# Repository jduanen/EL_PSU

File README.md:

# EL_PSU
High Voltage Power Supply Unit for EL Displays

This is a modification of the most excellent work of Ben Krasnow at https://github.com/benkrasnow/EL_driver_multi

The primary motivation for these changes are to better support the needs of the EL displays found in https://github.com/jduanen/alienFontDisplay and https://github.com/jduanen/elClock.
In particular, to extend the life of these displays, I want to create a triangle (as opposed to, step) waveform so that the dv/dt of the signal exciting the display segments remains (close to) constant.

**WIP**

#### Parts Kitting

* Digikey Cart: https://www.digikey.com/short/m9prqmhq
  - look at datasheets and make sure substitutions work
    * B0540W Schottky diode not in stock at Digikey, substituting B0540W RHG
    * MMBD5004S-7DICT-ND is an obsolete item at Digikey

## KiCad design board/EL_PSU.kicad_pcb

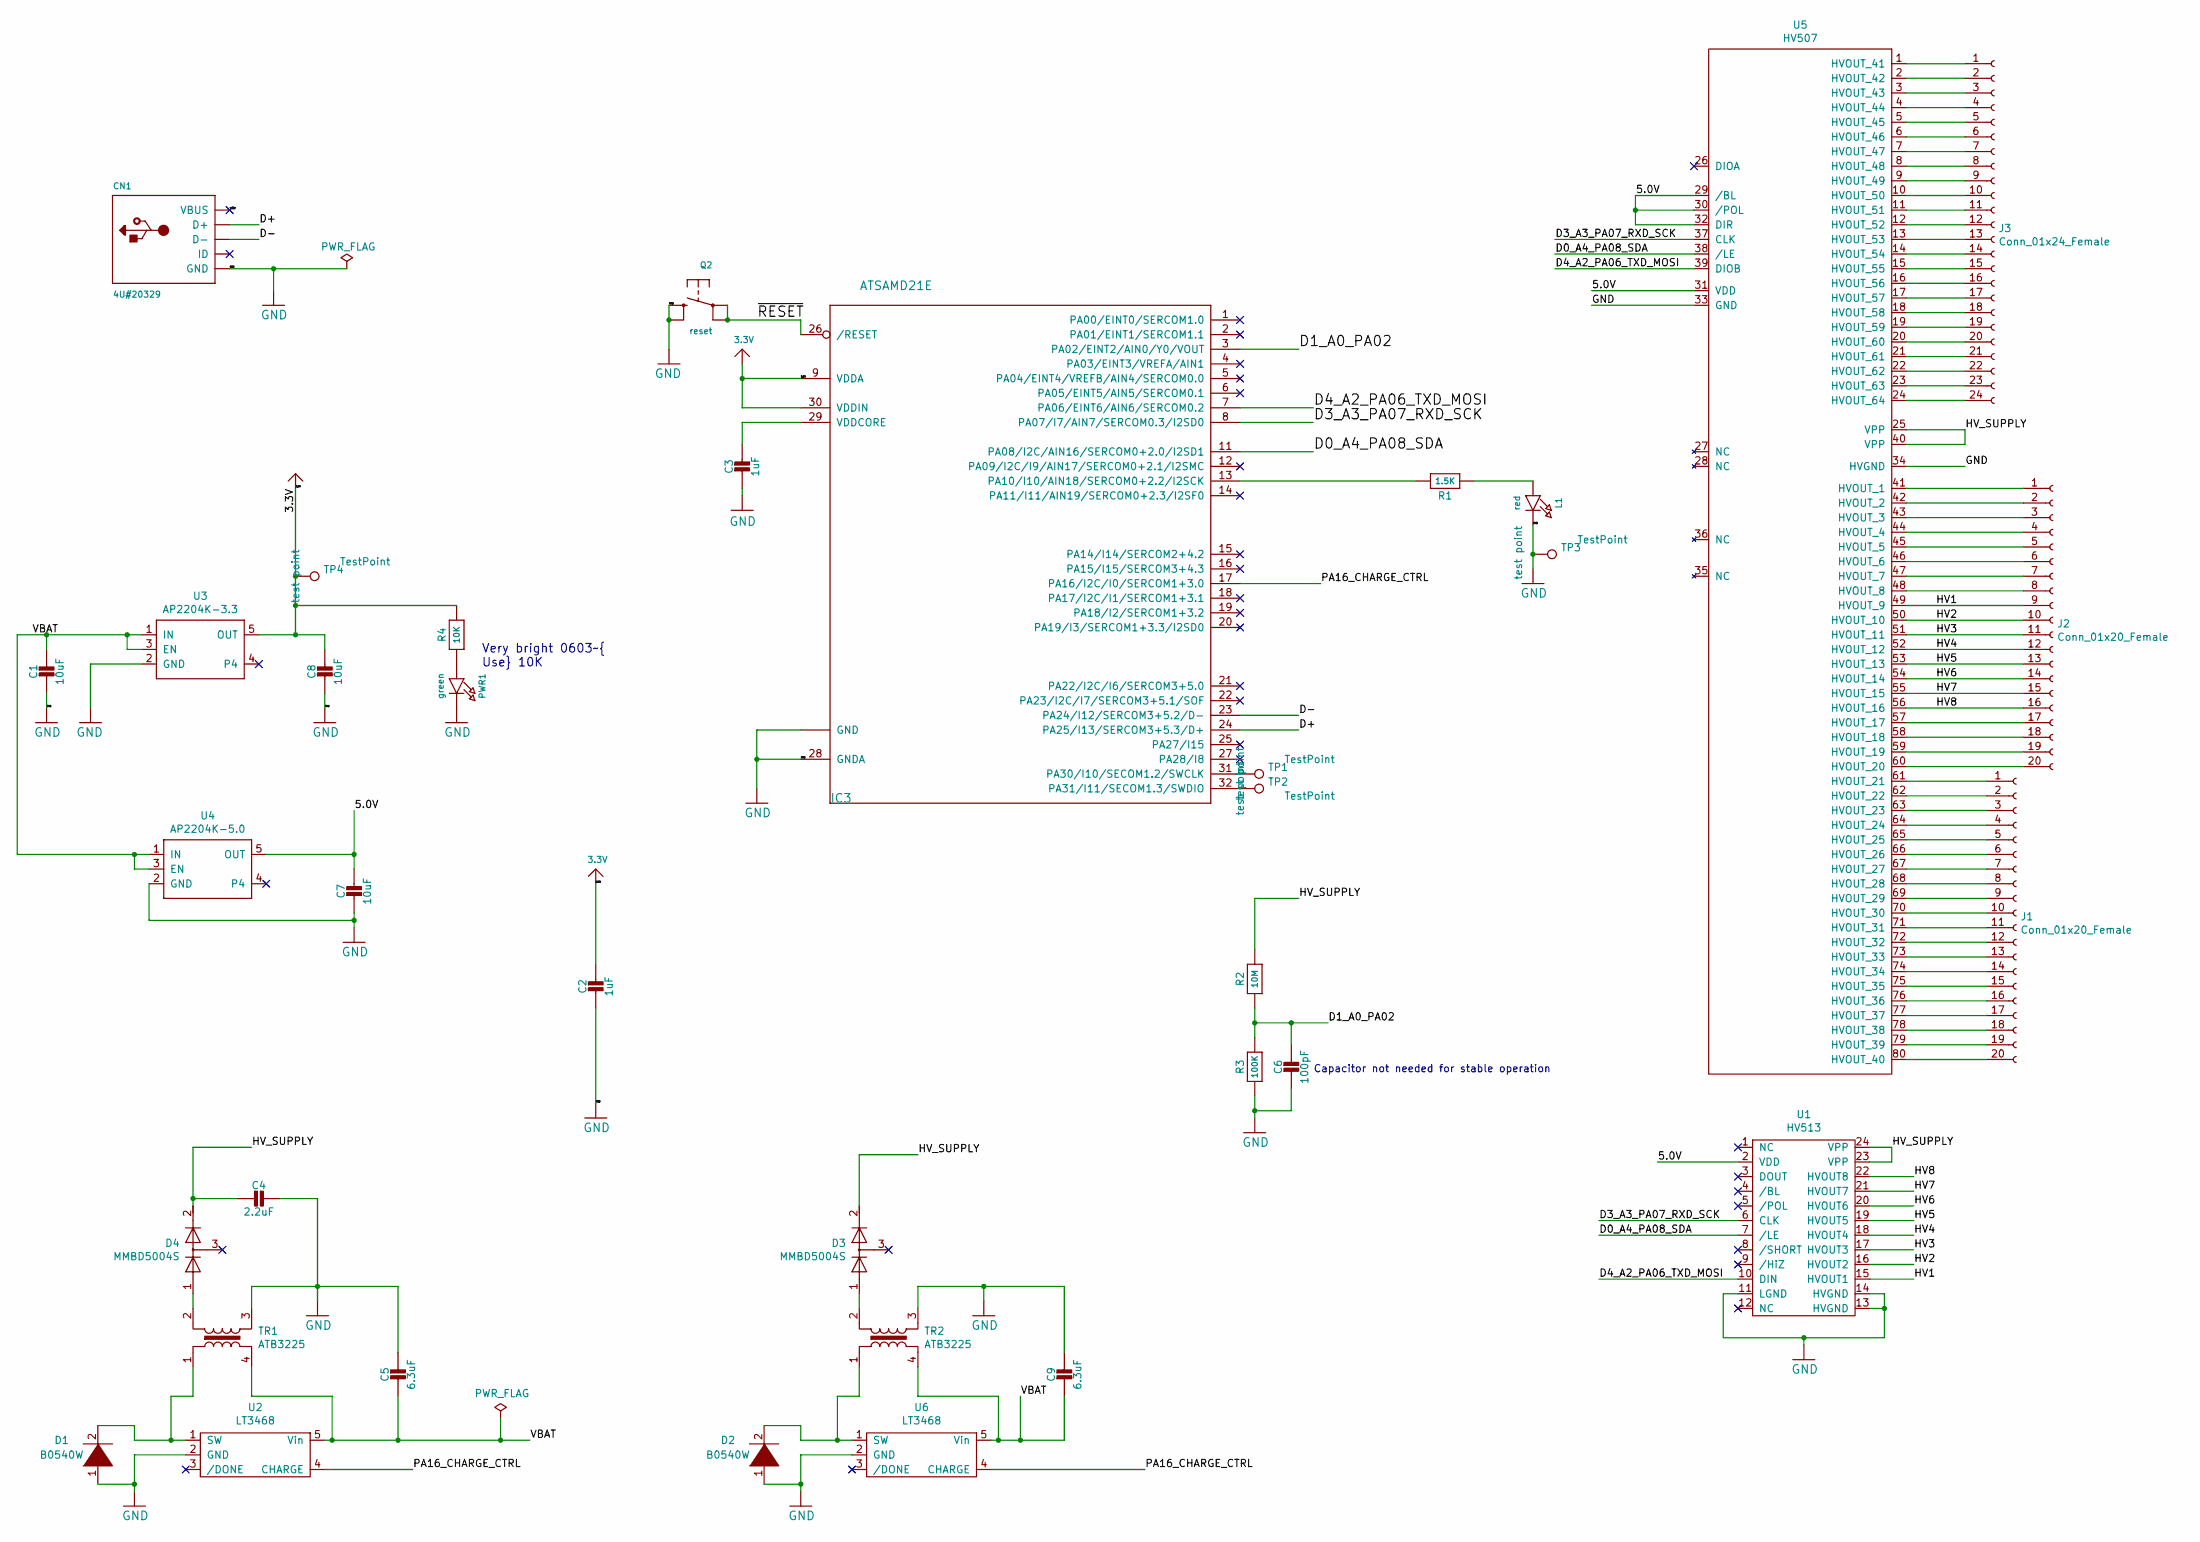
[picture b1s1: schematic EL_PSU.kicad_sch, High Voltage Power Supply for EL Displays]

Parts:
C1, C7, C8: 10uF; 0805-NO
C2, C3: 1uF; 0603-NO
C4: 2.2uF; C_2220_5650Metric
C5, C9: 6.3uF; 0603-NO
C6: 100pF; 0603-NO
CN1: 4U#20329; 4UCONN_20329_V2
D1, D2: B0540W; D_SOD-123
D3, D4: MMBD5004S; SOT-23
IC3: ATSAMD21E; QFN32_5MM
J1, J2: Conn_01x20_Female; PinHeader_1x20_P1.27mm_Vertical
J3: Conn_01x24_Female; PinHeader_1x24_P1.27mm_Vertical
L1: red; CHIPLED_0603_NOOUTLINE
PWR1: green; CHIPLED_0603_NOOUTLINE
Q2: reset; BTN_KMR2_4.6X2.8
R1: 1.5K; 0603-NO
R2: 10M; 0603-NO
R3: 100K; 0603-NO
R4: 10K; 0603-NO
TP1, TP2, TP3, TP4: TestPoint; TestPoint_Pad_D1.0mm
TR1, TR2: ATB3225
U1: HV513; SOIC-24W_7.5x15.4mm_P1.27mm
U2, U6: LT3468; SOT-23-5
U3: AP2204K-3.3; SOT-23-5
U4: AP2204K-5.0; SOT-23-5
U5: HV507; QFP-96_14x20_Pitch0.8mm

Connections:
3.3V: C2.1, C8.1, IC3.9 (VDDA), IC3.30 (VDDIN), R4.2, TP4.1, U3.5 (OUT)
/5.0V: C7.1, U1.2 (VDD), U4.5 (OUT), U5.29 (/BL), U5.30 (/POL), U5.31 (VDD), U5.32 (DIR)
/D0_A4_PA08_SDA: IC3.11 (PA08/I2C/AIN16/SERCOM0+2.0/I2SD1), U1.7 (/LE), U5.38 (/LE)
/D1_A0_PA02: C6.1, IC3.3 (PA02/EINT2/AIN0/Y0/VOUT), R2.1, R3.2
/D3_A3_PA07_RXD_SCK: IC3.8 (PA07/I7/AIN7/SERCOM0.3/I2SD0), U1.6 (CLK), U5.37 (CLK)
/D4_A2_PA06_TXD_MOSI: IC3.7 (PA06/EINT6/AIN6/SERCOM0.2), U1.10 (DIN), U5.39 (DIOB)
/D+: CN1.D+, IC3.24 (PA25/I13/SERCOM3+5.3/D+)
/D-: CN1.D-, IC3.23 (PA24/I12/SERCOM3+5.2/D-)
/HV1: J2.9, U1.15 (HVOUT1), U5.49 (HVOUT_9)
/HV2: J2.10, U1.16 (HVOUT2), U5.50 (HVOUT_10)
/HV3: J2.11, U1.17 (HVOUT3), U5.51 (HVOUT_11)
/HV4: J2.12, U1.18 (HVOUT4), U5.52 (HVOUT_12)
/HV5: J2.13, U1.19 (HVOUT5), U5.53 (HVOUT_13)
/HV6: J2.14, U1.20 (HVOUT6), U5.54 (HVOUT_14)
/HV7: J2.15, U1.21 (HVOUT7), U5.55 (HVOUT_15)
/HV8: J2.16, U1.22 (HVOUT8), U5.56 (HVOUT_16)
/HV_SUPPLY: C4.2, D3.2, D4.2, R2.2, U1.23 (VPP), U1.24 (VPP), U5.25 (VPP), U5.40 (VPP)
/PA16_CHARGE_CTRL: IC3.17 (PA16/I2C/I0/SERCOM1+3.0), U2.4 (CHARGE), U6.4 (CHARGE)
/VBAT: C1.1, C5.2, C9.2, TR1.4, TR2.4, U2.5 (Vin), U3.1 (IN), U3.3 (EN), U4.1 (IN), U4.3 (EN), U6.5 (Vin)
/VBUS: CN1.VBUS
/~RESET: IC3.26 (/RESET), Q2.A, Q2.A' (P1)
GND: C1.2, C2.2, C3.2, C4.1, C5.1, C6.2, C7.2, C8.2, C9.1, CN1.BASE@1 (GND), CN1.BASE@2 (GND), CN1.GND, CN1.SPRT@1 (GND), CN1.SPRT@2 (GND), CN1.SPRT@3 (GND), CN1.SPRT@4 (GND), D1.1 (K), D2.1 (K), IC3.10 (GND), IC3.28 (GNDA), IC3.33 (GND), L1.C, PWR1.C, Q2.B (S), Q2.B' (S1), R3.1, TP3.1, TR1.3, TR2.3, U1.11 (LGND), U1.13 (HVGND), U1.14 (HVGND), U2.2 (GND), U3.2 (GND), U4.2 (GND), U5.33 (GND), U5.34 (HVGND), U6.2 (GND)
unnamed: D1.2 (A), TR1.1, U2.1 (SW)
unnamed: D2.2 (A), TR2.1, U6.1 (SW)
unnamed: D3.1, TR2.2
unnamed: D4.1, TR1.2
unnamed: IC3.13 (PA10/I10/AIN18/SERCOM0+2.2/I2SCK), R1.2
unnamed: IC3.31 (PA30/I10/SECOM1.2/SWCLK), TP1.1
unnamed: IC3.32 (PA31/I11/SECOM1.3/SWDIO), TP2.1
unnamed: C3.1, IC3.29 (VDDCORE)
unnamed: J1.1, U5.61 (HVOUT_21)
unnamed: J1.2, U5.62 (HVOUT_22)
unnamed: J1.3, U5.63 (HVOUT_23)
unnamed: J1.4, U5.64 (HVOUT_24)
unnamed: J1.5, U5.65 (HVOUT_25)
unnamed: J1.6, U5.66 (HVOUT_26)
unnamed: J1.7, U5.67 (HVOUT_27)
unnamed: J1.8, U5.68 (HVOUT_28)
unnamed: J1.9, U5.69 (HVOUT_29)
unnamed: J1.10, U5.70 (HVOUT_30)
unnamed: J1.11, U5.71 (HVOUT_31)
unnamed: J1.12, U5.72 (HVOUT_32)
unnamed: J1.13, U5.73 (HVOUT_33)
unnamed: J1.14, U5.74 (HVOUT_34)
unnamed: J1.15, U5.75 (HVOUT_35)
unnamed: J1.16, U5.76 (HVOUT_36)
unnamed: J1.17, U5.77 (HVOUT_37)
unnamed: J1.18, U5.78 (HVOUT_38)
unnamed: J1.19, U5.79 (HVOUT_39)
unnamed: J1.20, U5.80 (HVOUT_40)
unnamed: J2.1, U5.41 (HVOUT_1)
unnamed: J2.2, U5.42 (HVOUT_2)
unnamed: J2.3, U5.43 (HVOUT_3)
unnamed: J2.4, U5.44 (HVOUT_4)
unnamed: J2.5, U5.45 (HVOUT_5)
unnamed: J2.6, U5.46 (HVOUT_6)
unnamed: J2.7, U5.47 (HVOUT_7)
unnamed: J2.8, U5.48 (HVOUT_8)
unnamed: J2.17, U5.57 (HVOUT_17)
unnamed: J2.18, U5.58 (HVOUT_18)
unnamed: J2.19, U5.59 (HVOUT_19)
unnamed: J2.20, U5.60 (HVOUT_20)
unnamed: J3.1, U5.1 (HVOUT_41)
unnamed: J3.2, U5.2 (HVOUT_42)
unnamed: J3.3, U5.3 (HVOUT_43)
unnamed: J3.4, U5.4 (HVOUT_44)
unnamed: J3.5, U5.5 (HVOUT_45)
unnamed: J3.6, U5.6 (HVOUT_46)
unnamed: J3.7, U5.7 (HVOUT_47)
unnamed: J3.8, U5.8 (HVOUT_48)
unnamed: J3.9, U5.9 (HVOUT_49)
unnamed: J3.10, U5.10 (HVOUT_50)
unnamed: J3.11, U5.11 (HVOUT_51)
unnamed: J3.12, U5.12 (HVOUT_52)
unnamed: J3.13, U5.13 (HVOUT_53)
unnamed: J3.14, U5.14 (HVOUT_54)
unnamed: J3.15, U5.15 (HVOUT_55)
unnamed: J3.16, U5.16 (HVOUT_56)
unnamed: J3.17, U5.17 (HVOUT_57)
unnamed: J3.18, U5.18 (HVOUT_58)
unnamed: J3.19, U5.19 (HVOUT_59)
unnamed: J3.20, U5.20 (HVOUT_60)
unnamed: J3.21, U5.21 (HVOUT_61)
unnamed: J3.22, U5.22 (HVOUT_62)
unnamed: J3.23, U5.23 (HVOUT_63)
unnamed: J3.24, U5.24 (HVOUT_64)
unnamed: L1.A, R1.1
unnamed: PWR1.A, R4.1

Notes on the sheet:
Very bright 0603~{ Use} 10K
Capacitor not needed for stable operation

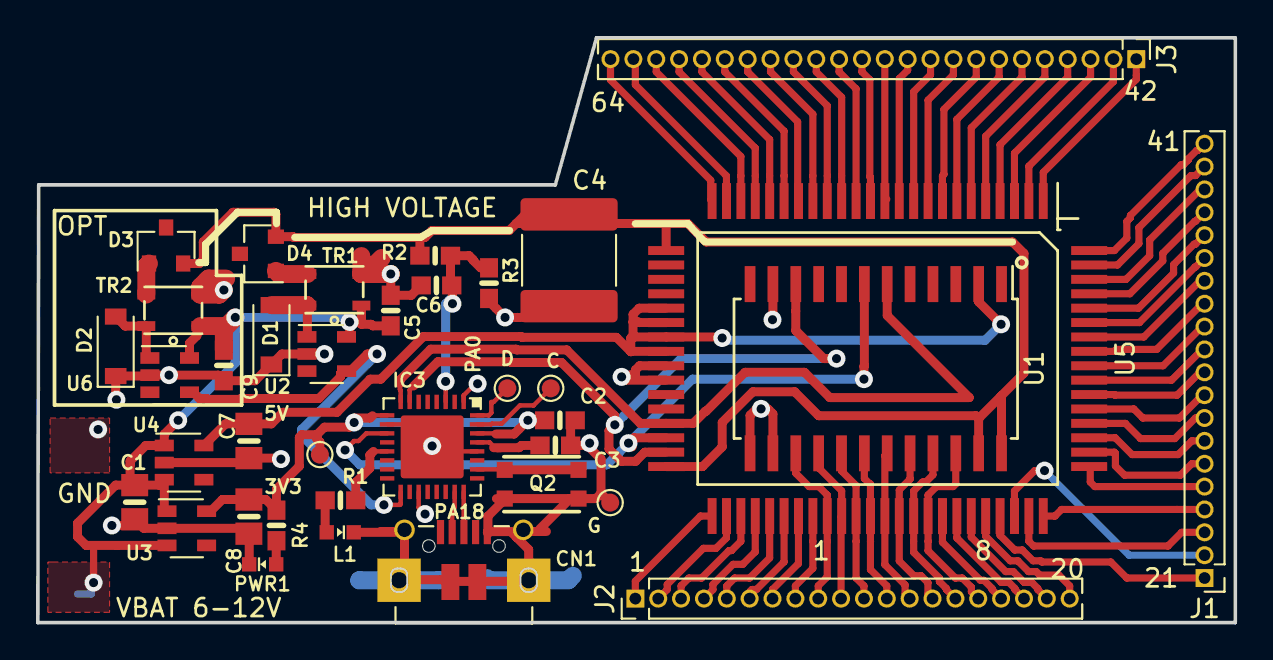
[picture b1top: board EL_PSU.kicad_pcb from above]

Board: 2 copper layers, 66.5 x 32.5 mm, 37 parts (0 on the bottom side), 87 nets.

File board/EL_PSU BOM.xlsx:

Reference | Value | Footprint | Datasheet | Qty | DNP | Exclude from BOM | Exclude from Board
C1,C7,C8 | 10uF | Trinket M0 rev D:0805-NO |  | 3.0
C2,C3 | 1uF | Trinket M0 rev D:0603-NO |  | 2.0
C5,C9 | 6.3uF | Trinket M0 rev D:0603-NO |  | 2.0
C6 | 100pF | Trinket M0 rev D:0603-NO |  | 1.0
CN1 | 4U#20329 | Trinket M0 rev D:4UCONN_20329_V2 |  | 1.0
IC3 | ATSAMD21E | Trinket M0 rev D:QFN32_5MM |  | 1.0
L1 | red | Trinket M0 rev D:CHIPLED_0603_NOOUTLINE |  | 1.0
PWR1 | green | Trinket M0 rev D:CHIPLED_0603_NOOUTLINE |  | 1.0
Q2 | reset | Trinket M0 rev D:BTN_KMR2_4.6X2.8 |  | 1.0
R1 | 1.5K | Trinket M0 rev D:0603-NO |  | 1.0
R2 | 10M | Trinket M0 rev D:0603-NO |  | 1.0
R3 | 100K | Trinket M0 rev D:0603-NO |  | 1.0
R4 | 10K | Trinket M0 rev D:0603-NO |  | 1.0
TR1,TR2 | ATB3225 | EL_driver:ATB3225 |  | 2.0
U2,U6 | LT3468 | Package_TO_SOT_SMD:SOT-23-5 |  | 2.0
U3 | AP2204K-3.3 | Package_TO_SOT_SMD:SOT-23-5 |  | 1.0
U4 | AP2204K-5.0 | Package_TO_SOT_SMD:SOT-23-5 |  | 1.0 |  | Diodes Incorporated | AP2210K-5.0TRG1
D1,D2 | B0540W | Diode_SMD:D_SOD-123 |  | 2.0
D3,D4 | MMBD5004S | Package_TO_SOT_SMD:SOT-23 |  | 2.0 |  | Toshiba | 1SS398TE85LF
TP1,TP2,TP3,TP4 | TestPoint | TestPoint:TestPoint_Pad_D1.0mm | ~ | 4.0
C4 | 2.2uF | Capacitor_SMD:C_2220_5650Metric |  | 1.0
J1,J2 | Conn_01x20_Female | Connector_PinHeader_1.27mm:PinHeader_1x20_P1.27mm_Vertical | ~ | 2.0
J3 | Conn_01x24_Female | Connector_PinHeader_1.27mm:PinHeader_1x24_P1.27mm_Vertical | ~ | 1.0
U1 | HV513 | Package_SO:SOIC-24W_7.5x15.4mm_P1.27mm |  | 1.0
U5 | HV507 | EL_driver:QFP-96_14x20_Pitch0.8mm |  | 1.0

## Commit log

2025-08-05 Copied from git@github.com:benkrasnow/EL_driver_multi.git.
2025-08-14 Updated.
2025-08-14 Removed. Not needed.
2025-08-14 Created.
2025-08-14 Added.
